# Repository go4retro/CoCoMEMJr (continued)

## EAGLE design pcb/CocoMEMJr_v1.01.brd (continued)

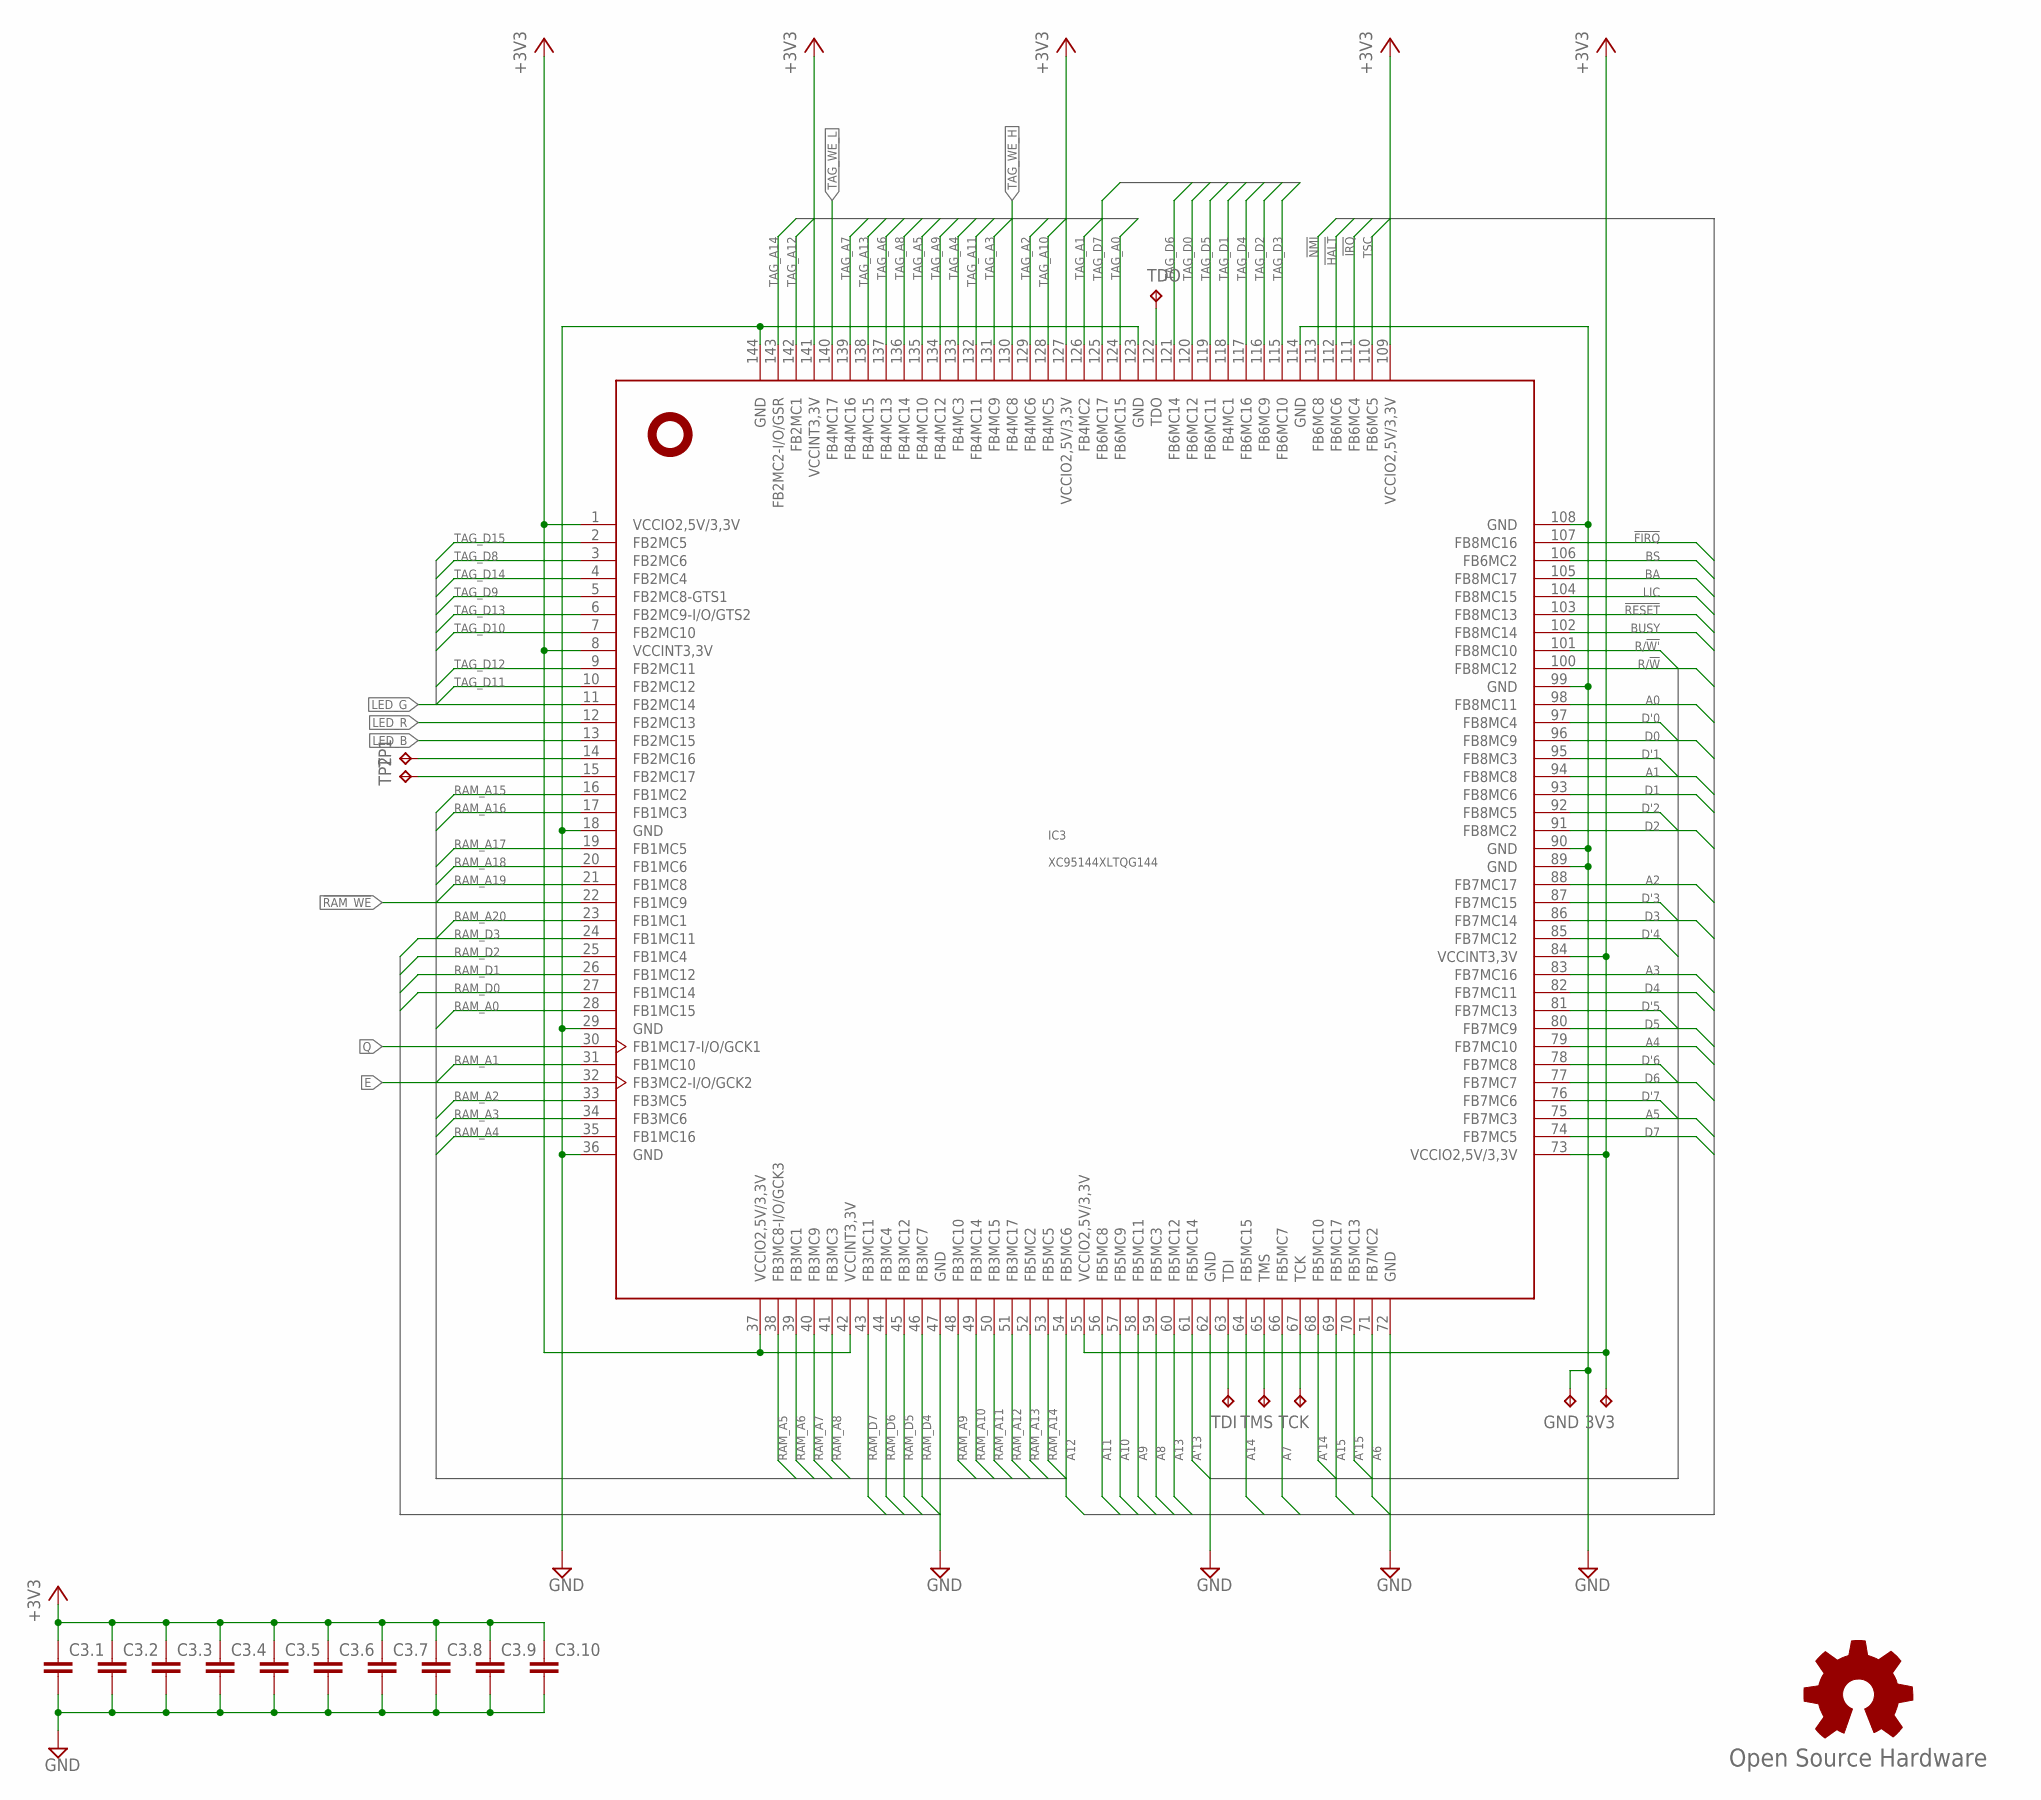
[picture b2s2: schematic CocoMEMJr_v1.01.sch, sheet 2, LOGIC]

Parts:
3V3: TPTP08R; TP08R
C3.1, C3.2, C3.3, C3.4, C3.5, C3.6, C3.7, C3.8, C3.9, C3.10: C-EUC0402; C0402
GND: TPTP08R; TP08R
GOLD_ORB_SM1: Open Source Hardware; OSHW_5MM
IC3: XC95144XLTQG144; TQFP144
TCK: TPTP08R; TP08R
TDI: TPTP08R; TP08R
TDO: TPTP08R; TP08R
TMS: TPTP08R; TP08R
TP1, TP2: TPTP08R; TP08R

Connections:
!FIRQ: IC3.107 (FB8MC16); also elsewhere on the board
!HALT: IC3.112 (FB6MC6); also elsewhere on the board
!IRQ: IC3.111 (FB6MC4); also elsewhere on the board
!NMI: IC3.113 (FB6MC8); also elsewhere on the board
!RAM_WE: IC3.22 (FB1MC9); also elsewhere on the board
!RESET: IC3.103 (FB8MC13); also elsewhere on the board
!TAG_WE_H: IC3.130 (FB4MC8); also elsewhere on the board
!TAG_WE_L: IC3.140 (FB4MC17); also elsewhere on the board
+3V3: 3V3.TP, C3.1.1, C3.2.1, C3.3.1, C3.4.1, C3.5.1, C3.6.1, C3.7.1, C3.8.1, C3.9.1, C3.10.1, IC3.1 (VCCIO2,5V/3,3V), IC3.8 (VCCINT3,3V), IC3.37 (VCCIO2,5V/3,3V), IC3.42 (VCCINT3,3V), IC3.55 (VCCIO2,5V/3,3V), IC3.73 (VCCIO2,5V/3,3V), IC3.84 (VCCINT3,3V), IC3.109 (VCCIO2,5V/3,3V), IC3.127 (VCCIO2,5V/3,3V), IC3.141 (VCCINT3,3V); also elsewhere on the board
A0: IC3.98 (FB8MC11); also elsewhere on the board
A1: IC3.94 (FB8MC8); also elsewhere on the board
A2: IC3.88 (FB7MC17); also elsewhere on the board
A3: IC3.83 (FB7MC16); also elsewhere on the board
A4: IC3.79 (FB7MC10); also elsewhere on the board
A5: IC3.75 (FB7MC3); also elsewhere on the board
A6: IC3.71 (FB7MC2); also elsewhere on the board
A7: IC3.66 (FB5MC7); also elsewhere on the board
A8: IC3.59 (FB5MC3); also elsewhere on the board
A9: IC3.58 (FB5MC11); also elsewhere on the board
A10: IC3.57 (FB5MC9); also elsewhere on the board
A11: IC3.56 (FB5MC8); also elsewhere on the board
A12: IC3.54 (FB5MC6); also elsewhere on the board
A13: IC3.60 (FB5MC12); also elsewhere on the board
A14: IC3.64 (FB5MC15); also elsewhere on the board
A15: IC3.69 (FB5MC17); also elsewhere on the board
A'13: IC3.61 (FB5MC14); also elsewhere on the board
A'14: IC3.68 (FB5MC10); also elsewhere on the board
A'15: IC3.70 (FB5MC13); also elsewhere on the board
BA: IC3.105 (FB8MC17); also elsewhere on the board
BS: IC3.106 (FB6MC2); also elsewhere on the board
BUSY: IC3.102 (FB8MC14); also elsewhere on the board
D0: IC3.96 (FB8MC9); also elsewhere on the board
D1: IC3.93 (FB8MC6); also elsewhere on the board
D2: IC3.91 (FB8MC2); also elsewhere on the board
D3: IC3.86 (FB7MC14); also elsewhere on the board
D4: IC3.82 (FB7MC11); also elsewhere on the board
D5: IC3.80 (FB7MC9); also elsewhere on the board
D6: IC3.77 (FB7MC7); also elsewhere on the board
D7: IC3.74 (FB7MC5); also elsewhere on the board
D'0: IC3.97 (FB8MC4); also elsewhere on the board
D'1: IC3.95 (FB8MC3); also elsewhere on the board
D'2: IC3.92 (FB8MC5); also elsewhere on the board
D'3: IC3.87 (FB7MC15); also elsewhere on the board
D'4: IC3.85 (FB7MC12); also elsewhere on the board
D'5: IC3.81 (FB7MC13); also elsewhere on the board
D'6: IC3.78 (FB7MC8); also elsewhere on the board
D'7: IC3.76 (FB7MC6); also elsewhere on the board
E: IC3.32 (FB3MC2-I/O/GCK2); also elsewhere on the board
GND: C3.1.2, C3.2.2, C3.3.2, C3.4.2, C3.5.2, C3.6.2, C3.7.2, C3.8.2, C3.9.2, C3.10.2, GND.TP, IC3.18 (GND), IC3.29 (GND), IC3.36 (GND), IC3.47 (GND), IC3.62 (GND), IC3.72 (GND), IC3.89 (GND), IC3.90 (GND), IC3.99 (GND), IC3.108 (GND), IC3.114 (GND), IC3.123 (GND), IC3.144 (GND); also elsewhere on the board
LED_B: IC3.13 (FB2MC15); also elsewhere on the board
LED_G: IC3.11 (FB2MC14); also elsewhere on the board
LED_R: IC3.12 (FB2MC13); also elsewhere on the board
LIC: IC3.104 (FB8MC15); also elsewhere on the board
unnamed: IC3.14 (FB2MC16), TP1.TP
unnamed: IC3.63 (TDI), TDI.TP
unnamed: IC3.65 (TMS), TMS.TP
unnamed: IC3.67 (TCK), TCK.TP
unnamed: IC3.122 (TDO), TDO.TP
unnamed: IC3.15 (FB2MC17), TP2.TP
Q: IC3.30 (FB1MC17-I/O/GCK1); also elsewhere on the board
R/!W: IC3.100 (FB8MC12); also elsewhere on the board
R/!W': IC3.101 (FB8MC10); also elsewhere on the board
RAM_A0: IC3.28 (FB1MC15); also elsewhere on the board
RAM_A1: IC3.31 (FB1MC10); also elsewhere on the board
RAM_A2: IC3.33 (FB3MC5); also elsewhere on the board
RAM_A3: IC3.34 (FB3MC6); also elsewhere on the board
RAM_A4: IC3.35 (FB1MC16); also elsewhere on the board
RAM_A5: IC3.38 (FB3MC8-I/O/GCK3); also elsewhere on the board
RAM_A6: IC3.39 (FB3MC1); also elsewhere on the board
RAM_A7: IC3.40 (FB3MC9); also elsewhere on the board
RAM_A8: IC3.41 (FB3MC3); also elsewhere on the board
RAM_A9: IC3.48 (FB3MC10); also elsewhere on the board
RAM_A10: IC3.49 (FB3MC14); also elsewhere on the board
RAM_A11: IC3.50 (FB3MC15); also elsewhere on the board
RAM_A12: IC3.51 (FB3MC17); also elsewhere on the board
RAM_A13: IC3.52 (FB5MC2); also elsewhere on the board
RAM_A14: IC3.53 (FB5MC5); also elsewhere on the board
RAM_A15: IC3.16 (FB1MC2); also elsewhere on the board
RAM_A16: IC3.17 (FB1MC3); also elsewhere on the board
RAM_A17: IC3.19 (FB1MC5); also elsewhere on the board
RAM_A18: IC3.20 (FB1MC6); also elsewhere on the board
RAM_A19: IC3.21 (FB1MC8); also elsewhere on the board
RAM_A20: IC3.23 (FB1MC1); also elsewhere on the board
RAM_D0: IC3.27 (FB1MC14); also elsewhere on the board
RAM_D1: IC3.26 (FB1MC12); also elsewhere on the board
RAM_D2: IC3.25 (FB1MC4); also elsewhere on the board
RAM_D3: IC3.24 (FB1MC11); also elsewhere on the board
RAM_D4: IC3.46 (FB3MC7); also elsewhere on the board
RAM_D5: IC3.45 (FB3MC12); also elsewhere on the board
RAM_D6: IC3.44 (FB3MC4); also elsewhere on the board
RAM_D7: IC3.43 (FB3MC11); also elsewhere on the board
TAG_A0: IC3.124 (FB6MC15); also elsewhere on the board
TAG_A1: IC3.126 (FB4MC2); also elsewhere on the board
TAG_A2: IC3.129 (FB4MC6); also elsewhere on the board
TAG_A3: IC3.131 (FB4MC9); also elsewhere on the board
TAG_A4: IC3.133 (FB4MC3); also elsewhere on the board
TAG_A5: IC3.135 (FB4MC10); also elsewhere on the board
TAG_A6: IC3.137 (FB4MC13); also elsewhere on the board
TAG_A7: IC3.139 (FB4MC16); also elsewhere on the board
TAG_A8: IC3.136 (FB4MC14); also elsewhere on the board
TAG_A9: IC3.134 (FB4MC12); also elsewhere on the board
TAG_A10: IC3.128 (FB4MC5); also elsewhere on the board
TAG_A11: IC3.132 (FB4MC11); also elsewhere on the board
TAG_A12: IC3.142 (FB2MC1); also elsewhere on the board
TAG_A13: IC3.138 (FB4MC15); also elsewhere on the board
TAG_A14: IC3.143 (FB2MC2-I/O/GSR); also elsewhere on the board
TAG_D0: IC3.120 (FB6MC12); also elsewhere on the board
TAG_D1: IC3.118 (FB4MC1); also elsewhere on the board
TAG_D2: IC3.116 (FB6MC9); also elsewhere on the board
TAG_D3: IC3.115 (FB6MC10); also elsewhere on the board
TAG_D4: IC3.117 (FB6MC16); also elsewhere on the board
TAG_D5: IC3.119 (FB6MC11); also elsewhere on the board
TAG_D6: IC3.121 (FB6MC14); also elsewhere on the board
TAG_D7: IC3.125 (FB6MC17); also elsewhere on the board
TAG_D8: IC3.3 (FB2MC6); also elsewhere on the board
TAG_D9: IC3.5 (FB2MC8-GTS1); also elsewhere on the board
TAG_D10: IC3.7 (FB2MC10); also elsewhere on the board
TAG_D11: IC3.10 (FB2MC12); also elsewhere on the board
TAG_D12: IC3.9 (FB2MC11); also elsewhere on the board
TAG_D13: IC3.6 (FB2MC9-I/O/GTS2); also elsewhere on the board
TAG_D14: IC3.4 (FB2MC4); also elsewhere on the board
TAG_D15: IC3.2 (FB2MC5); also elsewhere on the board
TSC: IC3.110 (FB6MC5); also elsewhere on the board

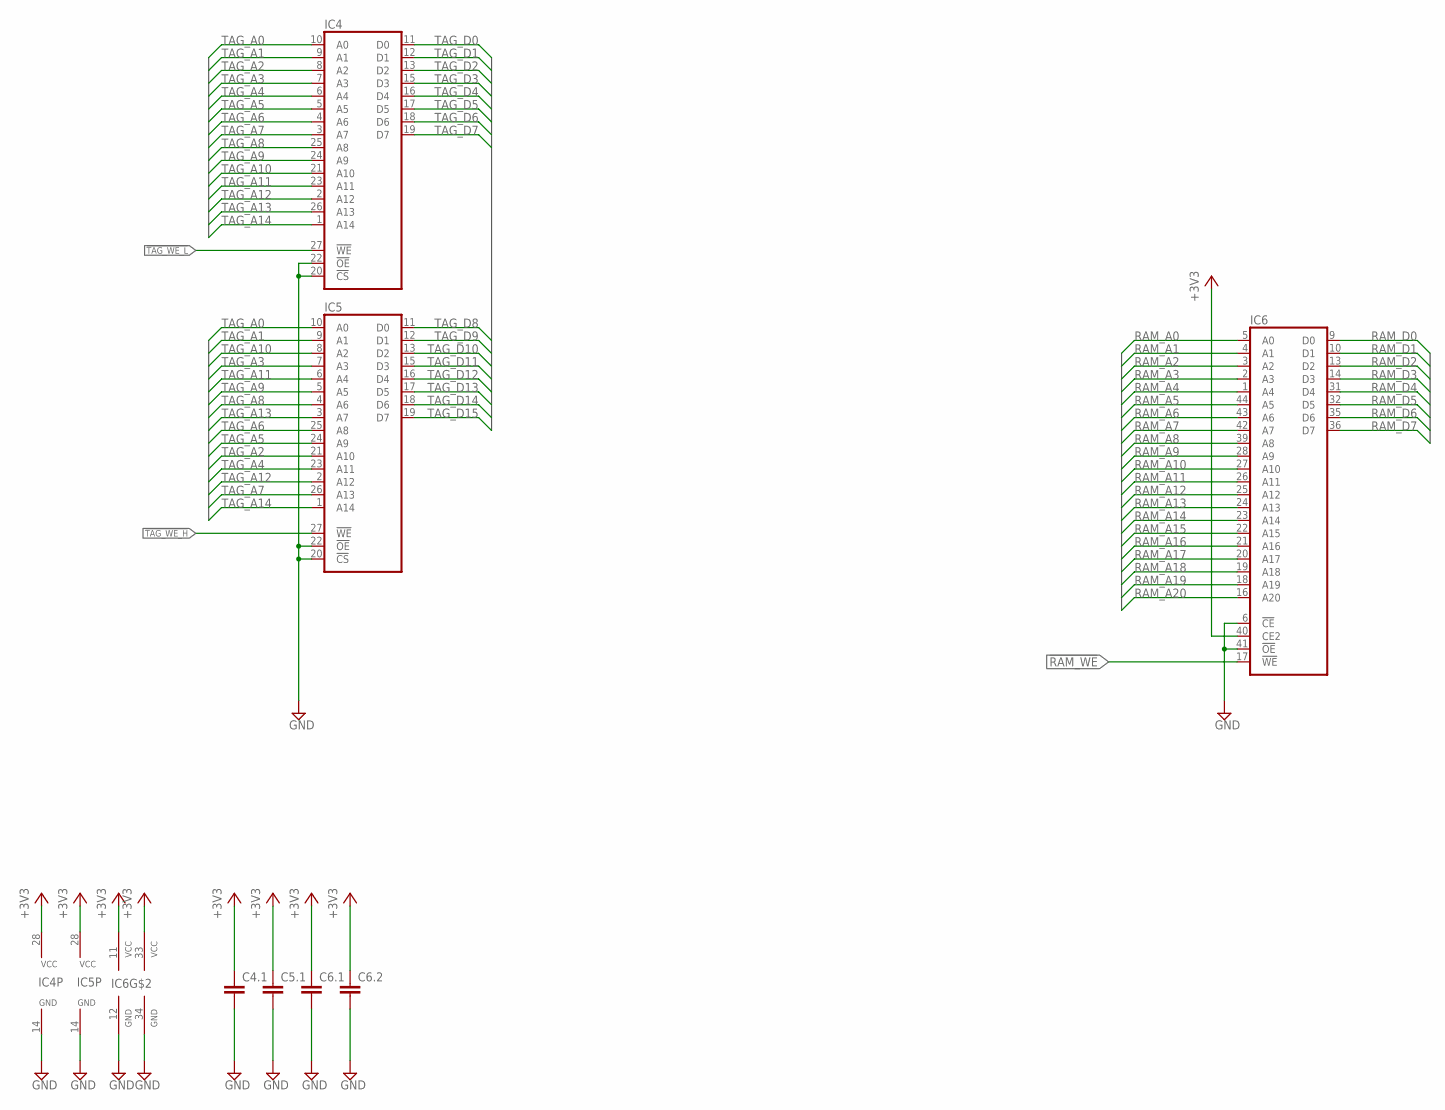
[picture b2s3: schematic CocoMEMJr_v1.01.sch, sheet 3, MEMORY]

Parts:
C4.1, C5.1, C6.1, C6.2: C-EUC0402; C0402
IC4, IC5: JEDEC_32KB_SRAMY; SOJ32/3
IC6: AS6C1608-XXTIN; TSOP44-II

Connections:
!RAM_WE: IC6.17 (!WE); also elsewhere on the board
!TAG_WE_H: IC5.27 (!WE); also elsewhere on the board
!TAG_WE_L: IC4.27 (!WE); also elsewhere on the board
+3V3: C4.1.1, C5.1.1, C6.1.1, C6.2.1, IC4.28 (VCC), IC5.28 (VCC), IC6.11 (VCC), IC6.33 (VCC), IC6.40 (CE2); also elsewhere on the board
GND: C4.1.2, C5.1.2, C6.1.2, C6.2.2, IC4.14 (GND), IC4.20 (!CS), IC4.22 (!OE), IC5.14 (GND), IC5.20 (!CS), IC5.22 (!OE), IC6.6 (!CE), IC6.12 (GND), IC6.34 (GND), IC6.41 (!OE); also elsewhere on the board
RAM_A0: IC6.5 (A0); also elsewhere on the board
RAM_A1: IC6.4 (A1); also elsewhere on the board
RAM_A2: IC6.3 (A2); also elsewhere on the board
RAM_A3: IC6.2 (A3); also elsewhere on the board
RAM_A4: IC6.1 (A4); also elsewhere on the board
RAM_A5: IC6.44 (A5); also elsewhere on the board
RAM_A6: IC6.43 (A6); also elsewhere on the board
RAM_A7: IC6.42 (A7); also elsewhere on the board
RAM_A8: IC6.39 (A8); also elsewhere on the board
RAM_A9: IC6.28 (A9); also elsewhere on the board
RAM_A10: IC6.27 (A10); also elsewhere on the board
RAM_A11: IC6.26 (A11); also elsewhere on the board
RAM_A12: IC6.25 (A12); also elsewhere on the board
RAM_A13: IC6.24 (A13); also elsewhere on the board
RAM_A14: IC6.23 (A14); also elsewhere on the board
RAM_A15: IC6.22 (A15); also elsewhere on the board
RAM_A16: IC6.21 (A16); also elsewhere on the board
RAM_A17: IC6.20 (A17); also elsewhere on the board
RAM_A18: IC6.19 (A18); also elsewhere on the board
RAM_A19: IC6.18 (A19); also elsewhere on the board
RAM_A20: IC6.16 (A20); also elsewhere on the board
RAM_D0: IC6.9 (D0); also elsewhere on the board
RAM_D1: IC6.10 (D1); also elsewhere on the board
RAM_D2: IC6.13 (D2); also elsewhere on the board
RAM_D3: IC6.14 (D3); also elsewhere on the board
RAM_D4: IC6.31 (D4); also elsewhere on the board
RAM_D5: IC6.32 (D5); also elsewhere on the board
RAM_D6: IC6.35 (D6); also elsewhere on the board
RAM_D7: IC6.36 (D7); also elsewhere on the board
TAG_A0: IC4.10 (A0), IC5.10 (A0); also elsewhere on the board
TAG_A1: IC4.9 (A1), IC5.9 (A1); also elsewhere on the board
TAG_A2: IC4.8 (A2), IC5.21 (A10); also elsewhere on the board
TAG_A3: IC4.7 (A3), IC5.7 (A3); also elsewhere on the board
TAG_A4: IC4.6 (A4), IC5.23 (A11); also elsewhere on the board
TAG_A5: IC4.5 (A5), IC5.24 (A9); also elsewhere on the board
TAG_A6: IC4.4 (A6), IC5.25 (A8); also elsewhere on the board
TAG_A7: IC4.3 (A7), IC5.26 (A13); also elsewhere on the board
TAG_A8: IC4.25 (A8), IC5.4 (A6); also elsewhere on the board
TAG_A9: IC4.24 (A9), IC5.5 (A5); also elsewhere on the board
TAG_A10: IC4.21 (A10), IC5.8 (A2); also elsewhere on the board
TAG_A11: IC4.23 (A11), IC5.6 (A4); also elsewhere on the board
TAG_A12: IC4.2 (A12), IC5.2 (A12); also elsewhere on the board
TAG_A13: IC4.26 (A13), IC5.3 (A7); also elsewhere on the board
TAG_A14: IC4.1 (A14), IC5.1 (A14); also elsewhere on the board
TAG_D0: IC4.11 (D0); also elsewhere on the board
TAG_D1: IC4.12 (D1); also elsewhere on the board
TAG_D2: IC4.13 (D2); also elsewhere on the board
TAG_D3: IC4.15 (D3); also elsewhere on the board
TAG_D4: IC4.16 (D4); also elsewhere on the board
TAG_D5: IC4.17 (D5); also elsewhere on the board
TAG_D6: IC4.18 (D6); also elsewhere on the board
TAG_D7: IC4.19 (D7); also elsewhere on the board
TAG_D8: IC5.11 (D0); also elsewhere on the board
TAG_D9: IC5.12 (D1); also elsewhere on the board
TAG_D10: IC5.13 (D2); also elsewhere on the board
TAG_D11: IC5.15 (D3); also elsewhere on the board
TAG_D12: IC5.16 (D4); also elsewhere on the board
TAG_D13: IC5.17 (D5); also elsewhere on the board
TAG_D14: IC5.18 (D6); also elsewhere on the board
TAG_D15: IC5.19 (D7); also elsewhere on the board

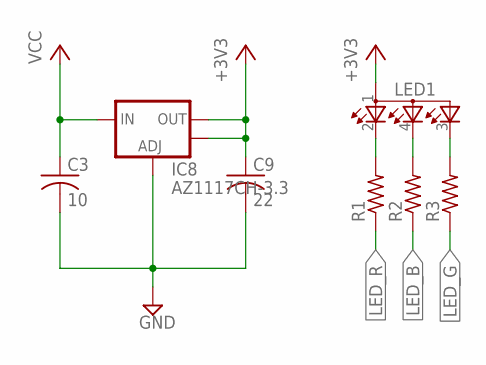
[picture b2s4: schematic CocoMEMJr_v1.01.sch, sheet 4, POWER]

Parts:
C3: 10; C0805
C9: 22; C0805
IC8: AZ1117CH-3.3; SOT223
LED1: RGBLED-PLCC4; PLCC-4
R1, R2, R3: R-US_R0402; R0402

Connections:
+3V3: C9.1, IC8.2 (OUT), IC8.4 (OUT), LED1.1 (A2); also elsewhere on the board
GND: C3.2, C9.2, IC8.1 (ADJ); also elsewhere on the board
LED_B: R2.1; also elsewhere on the board
LED_G: R3.1; also elsewhere on the board
LED_R: R1.1; also elsewhere on the board
unnamed: LED1.2 (CRED), R1.2
unnamed: LED1.4 (CBLUE), R2.2
unnamed: LED1.3 (CGREEN), R3.2
VCC: C3.1, IC8.3 (IN); also elsewhere on the board

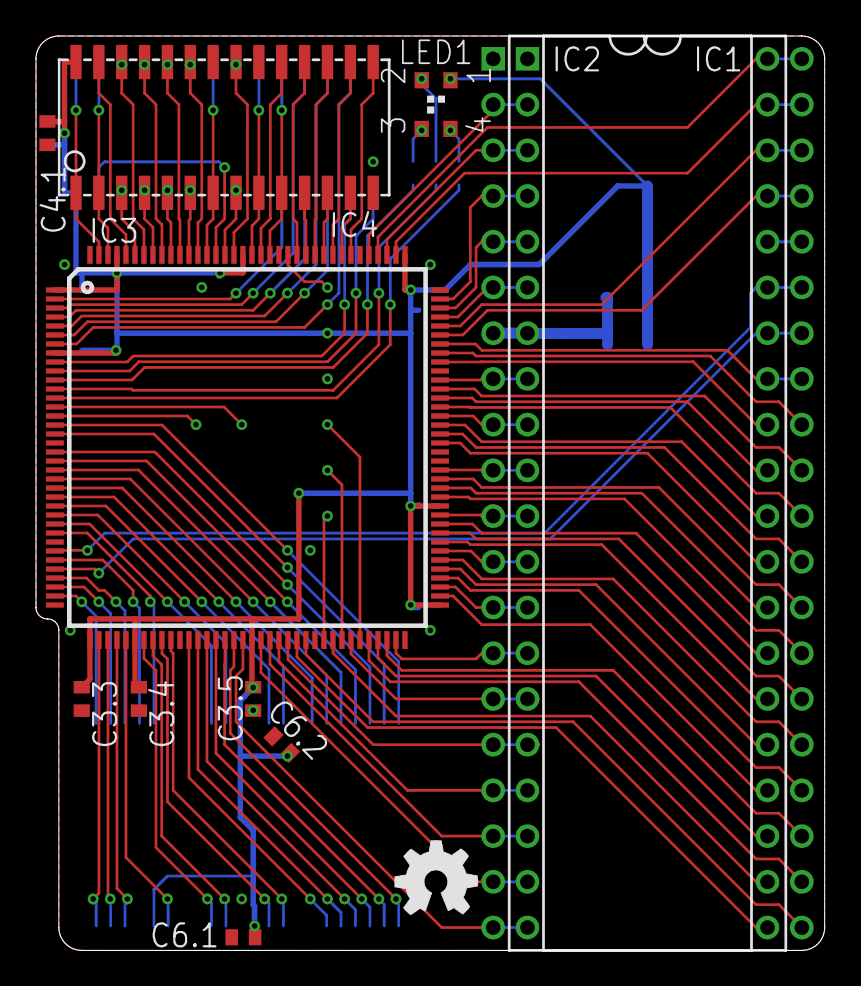
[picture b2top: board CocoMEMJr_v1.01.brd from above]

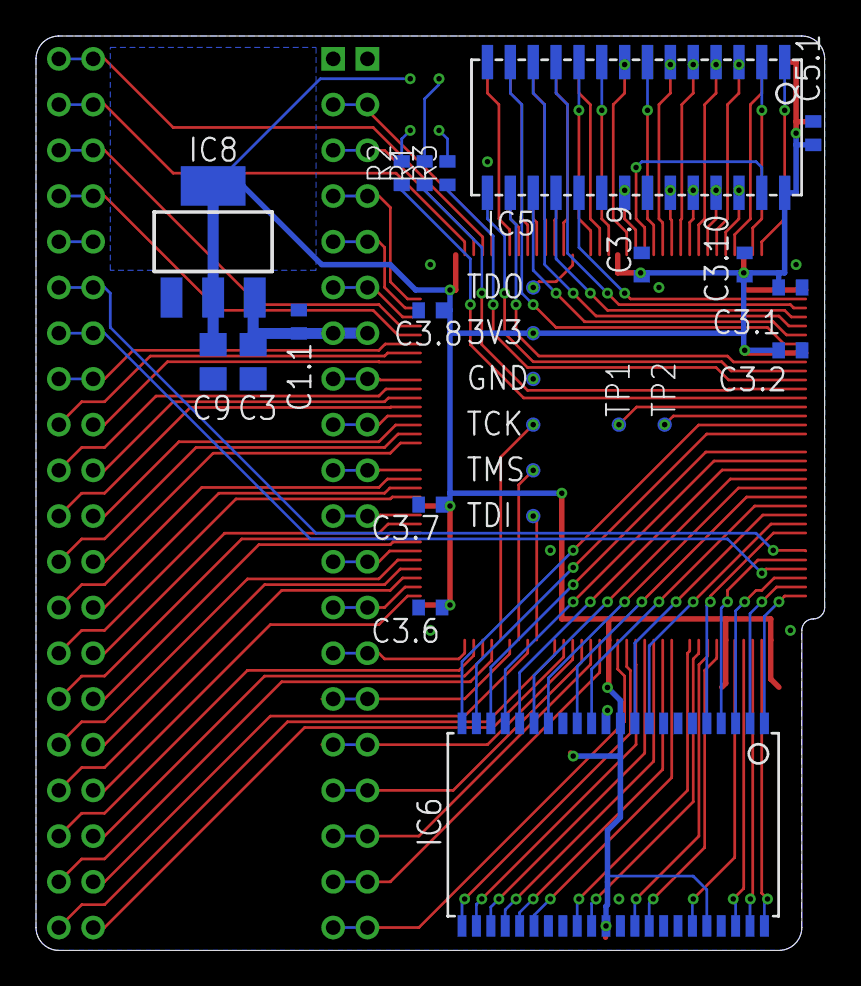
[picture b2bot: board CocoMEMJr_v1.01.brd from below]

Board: 2 copper layers, 43.8 x 50.8 mm, 37 parts (25 on the bottom side), 128 nets.

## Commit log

2018-03-26 Update license
2018-03-27 Added "windowing" and "word access" functionality for MMU page registers
2018-04-25 Cleaned up debug code and formalized alternate GIME register system
2018-04-28 Potential bug if user sets $ffa7 or $ffaf to 0-7 page and CRM is on, data will be stored in $00:fexx, not $3f:fexx
2018-11-14 Change Coco DRAM mapping from bank 0-7 to bank $38-$3f. Might need to change it back later.
2018-12-12 Fix errors introduced when moving internal DRAM from banks 0-7 to 38-3f
2019-03-02 Moved internal RAM back to banks 0-7, and added code to override $fffx vectors into bank $3f and read them from there.
2019-03-06 Fixed bug in ce_mem assignment (not qualifying with E clock)
2019-04-14 Potentially fixed MMU register windowing issue
2019-04-14 More fixes for MMU mapping
2019-12-01 Drive data lines on writes to motherboard only when e or q is high
2019-12-01 tristate address, data, and r/!w lines when BA = 1.
2019-12-02 CLeaned up a few equations
2025-08-30 Simplify the design for debugging
